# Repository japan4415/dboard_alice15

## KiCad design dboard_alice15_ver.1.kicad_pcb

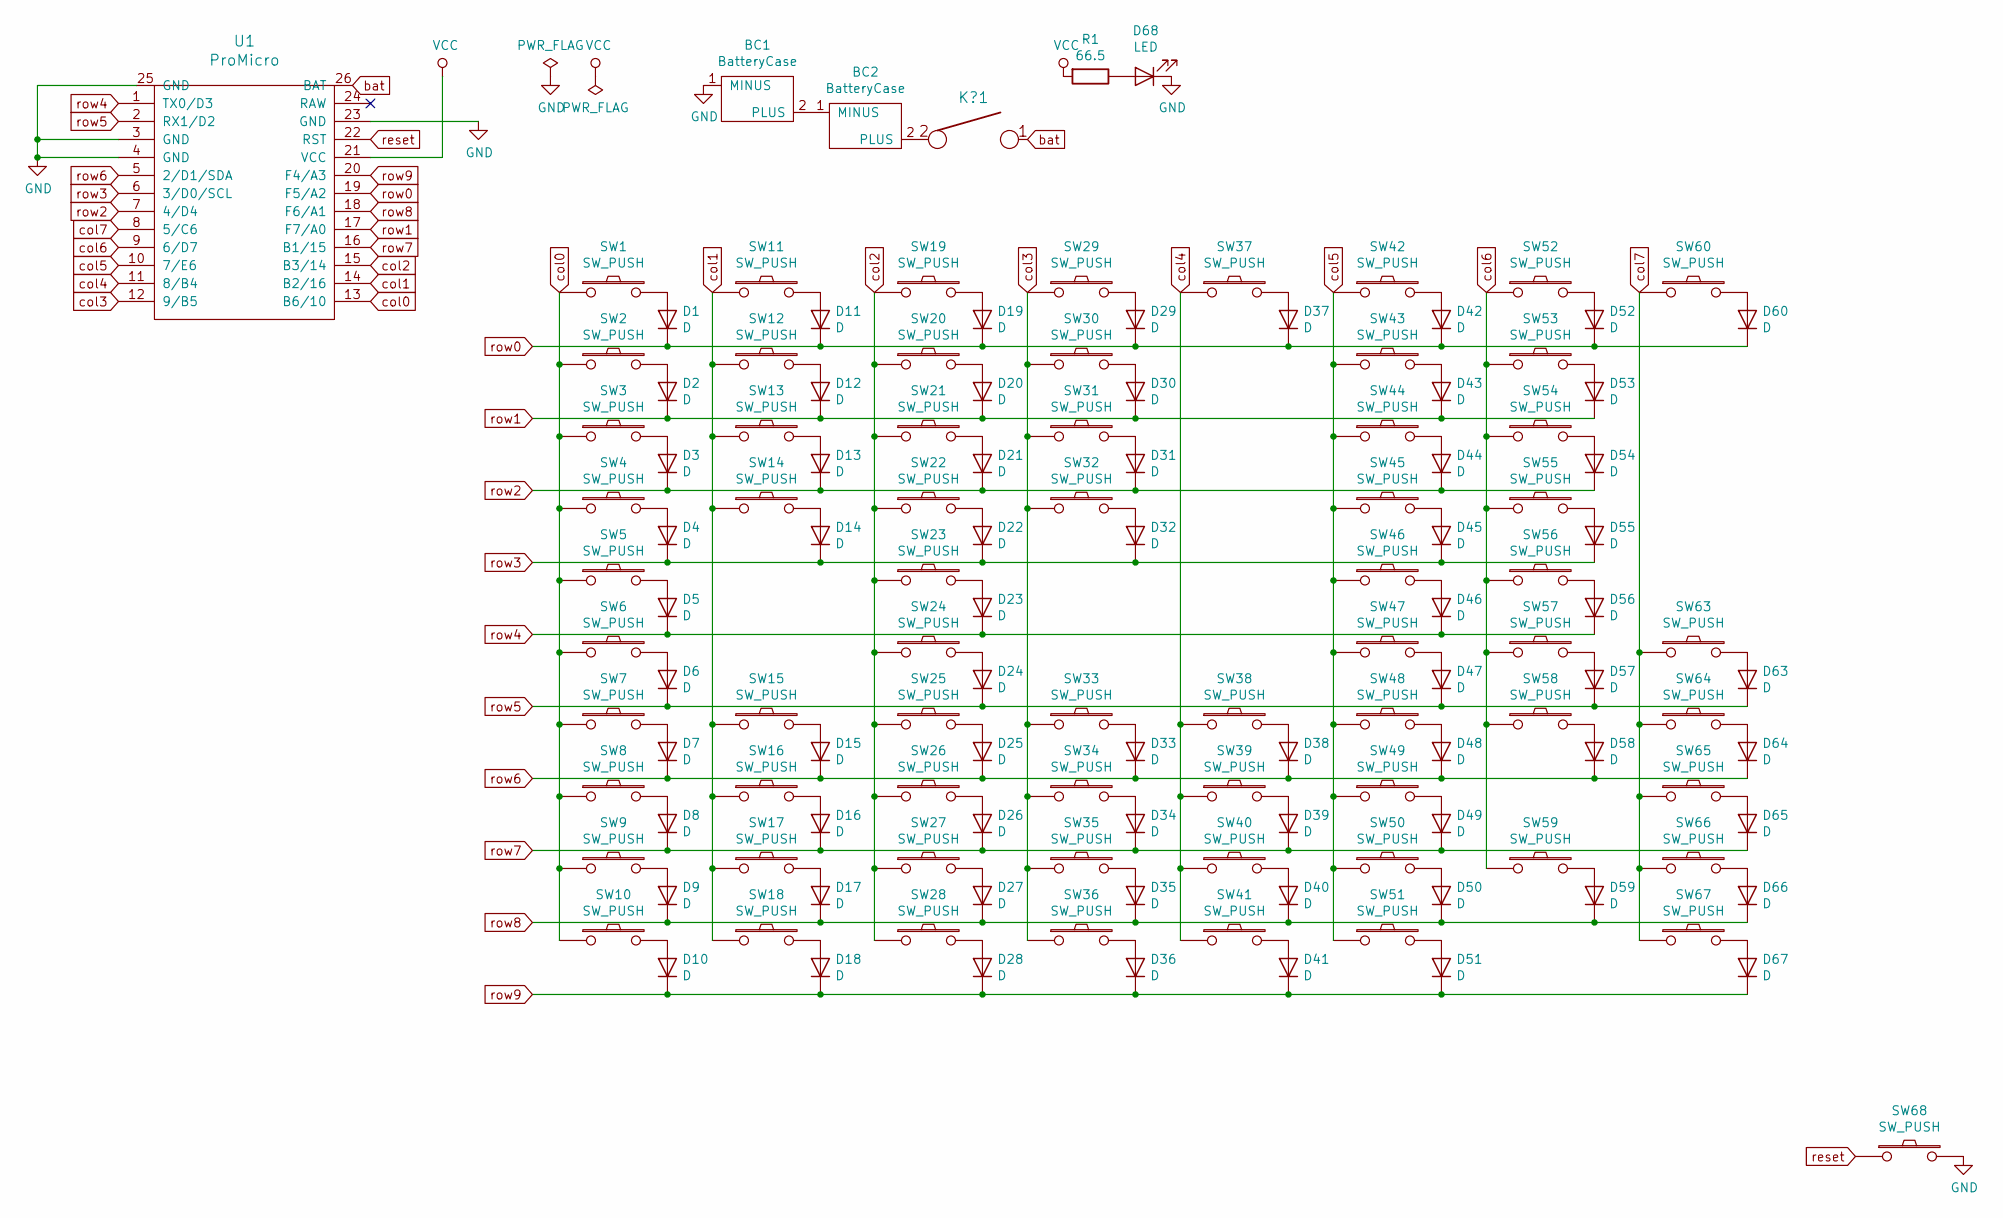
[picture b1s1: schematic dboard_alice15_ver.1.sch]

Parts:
BC1, BC2: BatteryCase; BatteryHolder_BK-82
D1, D2, D3, D4, D5, D6, D7, D8, D9, D10, D11, D12, D13, D14, D15, D16, D17, D18, D19, D20, D21, D22, D23, D24, D25, D26, D27, D28, D29, D30, D31, D32, D33, D34, D35, D36, D37, D38, D39, D40, D41, D42, D43, D44, D45, D46, D47, D48, D49, D50, D51, D52, D53, D54, D55, D56, D57, D58, D59, D60, D63, D64, D65, D66, D67: D; D_1206_3216Metric_Pad1.42x1.75mm_HandSolder
D68: LED; logo_LED_v1
K?1: KEYSW; GT11_MABE
R1: 66.5; R_1206_3216Metric_Pad1.42x1.75mm_HandSolder
SW1, SW2, SW3, SW4, SW7, SW8, SW9, SW10, SW11, SW12, SW13, SW14, SW15, SW16, SW17, SW18, SW19, SW20, SW21, SW22, SW25, SW26, SW27, SW28, SW29, SW30, SW31, SW32, SW33, SW34, SW35, SW36, SW37, SW38, SW39, SW40, SW41, SW42, SW43, SW44, SW45, SW47, SW48, SW49, SW50, SW51, SW52, SW57, SW58, SW59, SW60, SW63: SW_PUSH; Switch_MX_Alps_1U
SW5, SW6: SW_PUSH; Switch_MX_Alps_2.75U
SW23, SW24, SW46, SW56: SW_PUSH; Switch_MX_Alps_1.25U
SW53, SW66: SW_PUSH; Switch_MX_Alps_1.5U
SW54, SW64: SW_PUSH; Switch_MX_Alps_1.75U
SW55, SW65: SW_PUSH; Switch_MX_Alps_2.25U
SW67: SW_PUSH; Switch_MX_Alps_2U
SW68: SW_PUSH; Reset_Switch_from_Ali
U1: ProMicro; BLEMicroPro

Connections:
GND: BC1.1 (MINUS), D68.1 (K), SW68.2, U1.3 (GND), U1.4 (GND), U1.23 (GND), U1.25 (GND)
unnamed: BC1.2 (PLUS), BC2.1 (MINUS)
unnamed: BC2.2 (PLUS), K?1.2
unnamed: D1.2 (A), SW1.2
unnamed: D2.2 (A), SW2.2
unnamed: D3.2 (A), SW3.2
unnamed: D4.2 (A), SW4.2
unnamed: D5.2 (A), SW5.2
unnamed: D6.2 (A), SW6.2
unnamed: D7.2 (A), SW7.2
unnamed: D8.2 (A), SW8.2
unnamed: D9.2 (A), SW9.2
unnamed: D10.2 (A), SW10.2
unnamed: D11.2 (A), SW11.2
unnamed: D12.2 (A), SW12.2
unnamed: D13.2 (A), SW13.2
unnamed: D14.2 (A), SW14.2
unnamed: D15.2 (A), SW15.2
unnamed: D16.2 (A), SW16.2
unnamed: D17.2 (A), SW17.2
unnamed: D18.2 (A), SW18.2
unnamed: D19.2 (A), SW19.2
unnamed: D20.2 (A), SW20.2
unnamed: D21.2 (A), SW21.2
unnamed: D22.2 (A), SW22.2
unnamed: D23.2 (A), SW23.2
unnamed: D24.2 (A), SW24.2
unnamed: D25.2 (A), SW25.2
unnamed: D26.2 (A), SW26.2
unnamed: D27.2 (A), SW27.2
unnamed: D28.2 (A), SW28.2
unnamed: D29.2 (A), SW29.2
unnamed: D30.2 (A), SW30.2
unnamed: D31.2 (A), SW31.2
unnamed: D32.2 (A), SW32.2
unnamed: D33.2 (A), SW33.2
unnamed: D34.2 (A), SW34.2
unnamed: D35.2 (A), SW35.2
unnamed: D36.2 (A), SW36.2
unnamed: D37.2 (A), SW37.2
unnamed: D38.2 (A), SW38.2
unnamed: D39.2 (A), SW39.2
unnamed: D40.2 (A), SW40.2
unnamed: D41.2 (A), SW41.2
unnamed: D42.2 (A), SW42.2
unnamed: D43.2 (A), SW43.2
unnamed: D44.2 (A), SW44.2
unnamed: D45.2 (A), SW45.2
unnamed: D46.2 (A), SW46.2
unnamed: D47.2 (A), SW47.2
unnamed: D48.2 (A), SW48.2
unnamed: D49.2 (A), SW49.2
unnamed: D50.2 (A), SW50.2
unnamed: D51.2 (A), SW51.2
unnamed: D52.2 (A), SW52.2
unnamed: D53.2 (A), SW53.2
unnamed: D54.2 (A), SW54.2
unnamed: D55.2 (A), SW55.2
unnamed: D56.2 (A), SW56.2
unnamed: D57.2 (A), SW57.2
unnamed: D58.2 (A), SW58.2
unnamed: D59.2 (A), SW59.2
unnamed: D60.2 (A), SW60.2
unnamed: D63.2 (A), SW63.2
unnamed: D64.2 (A), SW64.2
unnamed: D65.2 (A), SW65.2
unnamed: D66.2 (A), SW66.2
unnamed: D67.2 (A), SW67.2
unnamed: D68.2 (A), R1.1
VCC: R1.2, U1.21 (VCC)
bat: K?1.1, U1.26 (BAT)
col0: SW1.1, SW2.1, SW3.1, SW4.1, SW5.1, SW6.1, SW7.1, SW8.1, SW9.1, SW10.1, U1.13 (B6/10)
col1: SW11.1, SW12.1, SW13.1, SW14.1, SW15.1, SW16.1, SW17.1, SW18.1, U1.14 (B2/16)
col2: SW19.1, SW20.1, SW21.1, SW22.1, SW23.1, SW24.1, SW25.1, SW26.1, SW27.1, SW28.1, U1.15 (B3/14)
col3: SW29.1, SW30.1, SW31.1, SW32.1, SW33.1, SW34.1, SW35.1, SW36.1, U1.12 (9/B5)
col4: SW37.1, SW38.1, SW39.1, SW40.1, SW41.1, U1.11 (8/B4)
col5: SW42.1, SW43.1, SW44.1, SW45.1, SW46.1, SW47.1, SW48.1, SW49.1, SW50.1, SW51.1, U1.10 (7/E6)
col6: SW52.1, SW53.1, SW54.1, SW55.1, SW56.1, SW57.1, SW58.1, SW59.1, U1.9 (6/D7)
col7: SW60.1, SW63.1, SW64.1, SW65.1, SW66.1, SW67.1, U1.8 (5/C6)
reset: SW68.1, U1.22 (RST)
row0: D1.1 (K), D11.1 (K), D19.1 (K), D29.1 (K), D37.1 (K), D42.1 (K), D52.1 (K), D60.1 (K), U1.19 (F5/A2)
row1: D2.1 (K), D12.1 (K), D20.1 (K), D30.1 (K), D43.1 (K), D53.1 (K), U1.17 (F7/A0)
row2: D3.1 (K), D13.1 (K), D21.1 (K), D31.1 (K), D44.1 (K), D54.1 (K), U1.7 (4/D4)
row3: D4.1 (K), D14.1 (K), D22.1 (K), D32.1 (K), D45.1 (K), D55.1 (K), U1.6 (3/D0/SCL)
row4: D5.1 (K), D23.1 (K), D46.1 (K), D56.1 (K), U1.1 (TX0/D3)
row5: D6.1 (K), D24.1 (K), D47.1 (K), D57.1 (K), D63.1 (K), U1.2 (RX1/D2)
row6: D7.1 (K), D15.1 (K), D25.1 (K), D33.1 (K), D38.1 (K), D48.1 (K), D58.1 (K), D64.1 (K), U1.5 (2/D1/SDA)
row7: D8.1 (K), D16.1 (K), D26.1 (K), D34.1 (K), D39.1 (K), D49.1 (K), D65.1 (K), U1.16 (B1/15)
row8: D9.1 (K), D17.1 (K), D27.1 (K), D35.1 (K), D40.1 (K), D50.1 (K), D59.1 (K), D66.1 (K), U1.18 (F6/A1)
row9: D10.1 (K), D18.1 (K), D28.1 (K), D36.1 (K), D41.1 (K), D51.1 (K), D67.1 (K), U1.20 (F4/A3)

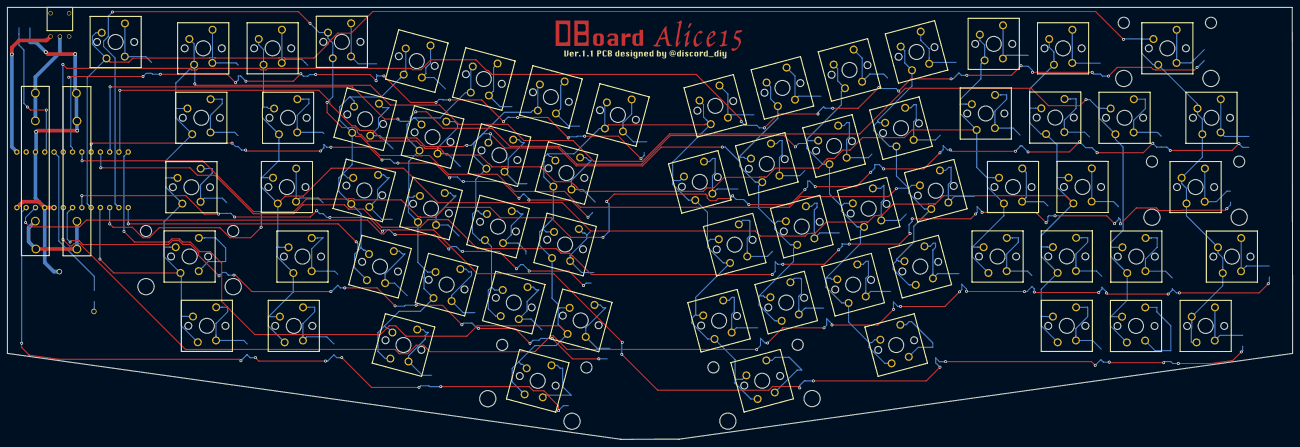
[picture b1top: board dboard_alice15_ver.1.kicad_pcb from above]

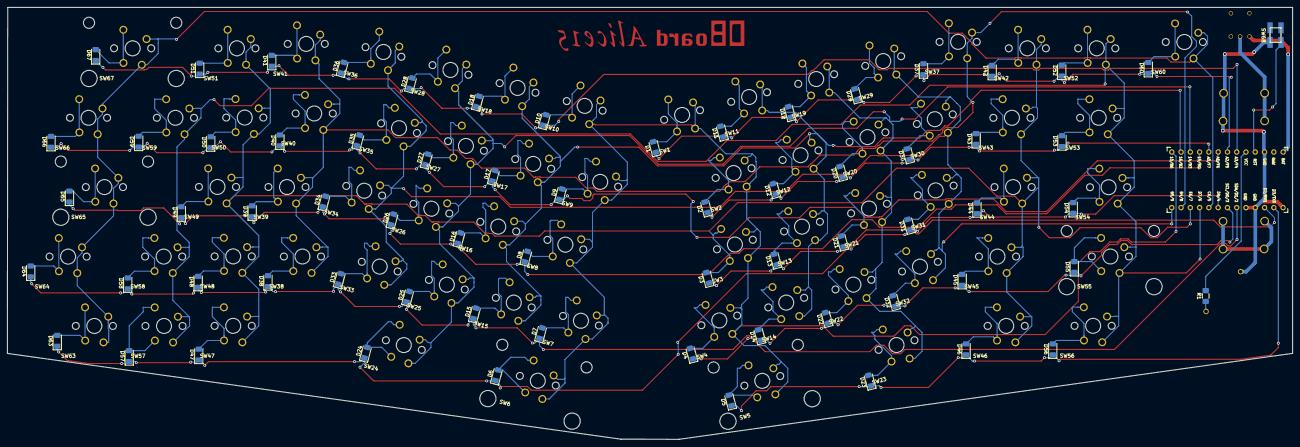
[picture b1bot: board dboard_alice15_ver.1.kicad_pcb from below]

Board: 2 copper layers, 351.8 x 118.2 mm, 137 parts (66 on the bottom side), 90 nets.

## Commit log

2020-08-24 add contents
